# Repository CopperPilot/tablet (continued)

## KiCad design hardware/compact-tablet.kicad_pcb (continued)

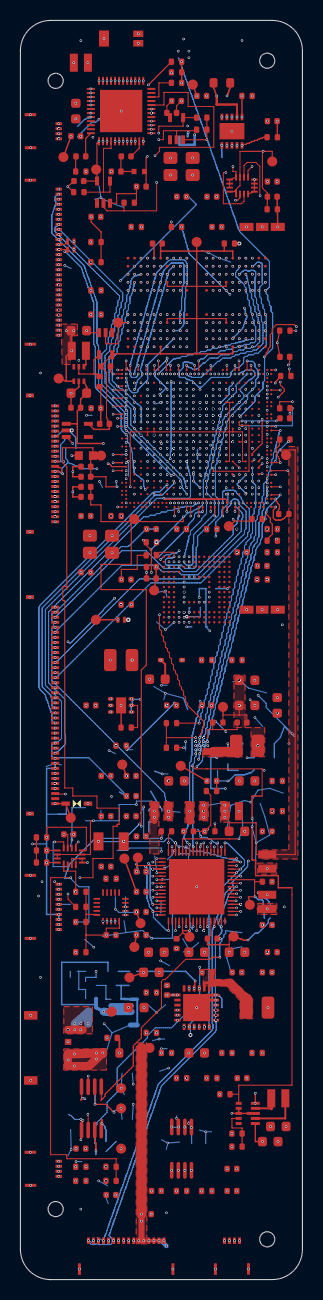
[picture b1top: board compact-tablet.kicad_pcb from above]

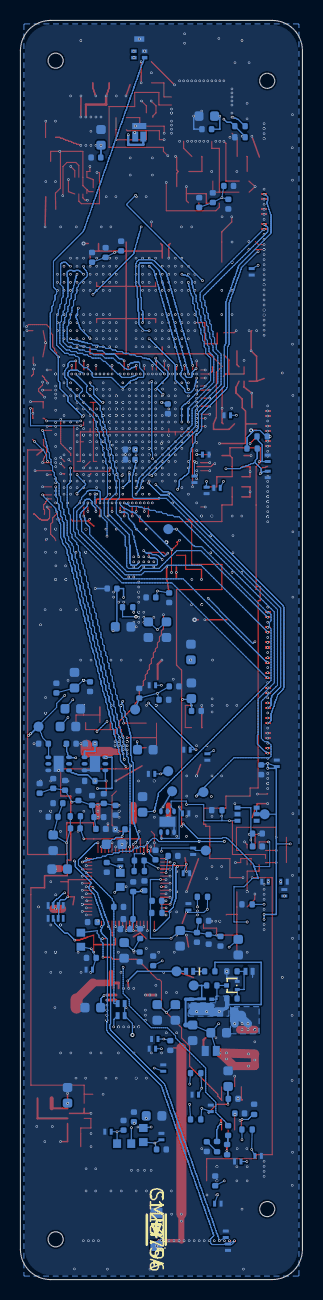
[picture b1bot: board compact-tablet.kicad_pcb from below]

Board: 8 copper layers, 28.0 x 125.0 mm, 431 parts (181 on the bottom side), 314 nets.

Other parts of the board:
H1, H2, H3, H4: MountingHole; MountingHole_1.5mm

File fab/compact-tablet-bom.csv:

Comment,Designator,Footprint,LCSC Part #
ANT3216A063R2400A,ANT1,ANT-SMD_3P-L3.1-W1.6_ANT3216A063R2400A,C412135
10uF,"C1,C2,C3,C4,C5,C6,C58,C63,C64,C70,C71,C82,C129,C130,C163,C165,C166,C167,C168,C178,C179,C180,C182",C_0603_1608Metric,C19702
1uF,"C7,C8,C9,C10,C11,C12,C29,C30,C31,C32,C33,C34,C36,C37,C38,C39,C40,C41,C43,C55,C59,C60,C62,C76,C77,C78,C79,C127,C128,C140,C142,C147,C148,C149,C151,C159,C160,C174,C177,C181,C183,C184",C_0402_1005Metric,C52923
100nF,"C13,C14,C15,C16,C17,C35,C42,C44,C45,C47,C48,C52,C56,C57,C61,C72,C75,C83,C84,C85,C86,C87,C88,C91,C92,C93,C94,C97,C98,C99,C100,C101,C105,C106,C107,C108,C109,C110,C111,C112,C113,C114,C115,C116,C117,C118,C119,C122,C123,C125,C126,C131,C132,C139,C141,C143,C144,C145,C146,C150,C152,C154,C156,C157,C158,C161,C162,C164,C169,C175,C176",C_0402_1005Metric,C1525
22uF,"C50,C51,C65,C80,C81,C89,C90,C95,C96,C102,C103,C104,C120,C121,C124",C_0603_1608Metric,C59461
1nF,"C53,C54,C73,C74,C133,C134,C135,C136,C137,C138",C_0402_1005Metric,C1523
4.7uF,"C28,C46,C153,C155",C_0603_1608Metric,C19666
10uF,"C170,C171,C172,C173",C_0402_1005Metric,C77000
2.2uF,C18,C_0402_1005Metric,C107369
1uF,C19,C_0603_1608Metric,C15849
15pF,"C20,C21,C22,C23,C24,C25",C_0402_1005Metric,C1548
10uF,C26,C_0603_1608Metric,C96446
47nF,C27,C_0402_1005Metric,C272875
4.7uF,C49,C_0402_1005Metric,C2858031
18pF,"C66,C67",C_0402_1005Metric,C1549
1.5pF,"C68,C69",C_0402_1005Metric,C1552
KW CELNM3.TK-S4S9-4L07M0-2686,D1,LED-SMD_3P-L1.9-W1.5_KW-CELMM1.TG,C17383700
"PESD5V0F1BL,315","D9,D10,D11,D12,D16,D19,D20,D21,D22,D23,D24,D25,D26,D27,D28,D32,D33,D34,D39,D40,D46,D47,D48",SOD-882_L1.0-W0.6-BI,C45961
SMF7.5A,D13,SOD-123F_L2.8-W1.8-LS3.7-RD,C123796
H36VND3B,D14,SOD-323_L1.8-W1.3-LS2.7-BI,C20615816
PTVS5V5D1BLYL,"D5,D6,D7,D8,D15,D17,D18,D29,D30,D31,D35,D36,D37,D38",SOD-882_L1.0-W0.6-BI-1,C553450
B16WS,D2,D_SOD-323,C364278
TPTVS0571P,D3,DFN-2_L1.6-W1.0-P1.10-RD,C2844712
"BAS70L,315","D43,D44,D45,D49",SOD-882_L1.0-W0.6-RD,C456141
BSMD0603L-300,F1,F0603,C5374008
FPC-0.5HF-40PWBH10,J1,FPC-SMD_40P-P0.50_FPC-0.5HF-40PWBH10,C5343289
0.5K-QX-10PWB,J2,FPC-SMD_10P-P0.50_HDGC_0.5K-QX-10PWB,C2919478
0.5K-QX-30PWB,J3,FPC-SMD_30P-P0.50_HDGC_0.5K-QX-30PWB,C2919487
FPC-0.5HF-24PWBH10,J4,FPC-SMD_24P-P0.50_XUNPU_FPC-0.5HF-24PWBH10,C5343283
DF58-4P-1.2V(21),J5,CONN-SMD_4P-P1.20_DF58-4P-1.2V-21,C20723302
0.5K-QX-16PWB,J6,FPC-SMD_16P-P0.50_HDGC_0.5K-QX-16PWB,C2919481
0.5K-QX-4PWB,"J7,J8,J9",FPC-SMD_4P-P0.50_HDGC_0.5K-QX-4PWB,C2919475
470nH,"L1,L2,L3,L4,L5",IND-SMD_L2.0-W1.6_WPN2016X,C97009
0.47uH,L10,IND-SMD_L2.0-W1.6_WPN2016X,C97009
2.2nH,L11,IND-SMD_L1.0-W0.5_LQG15HN1N6B02D,C86061
1uH,L12,IND-SMD_L2.0-W1.6_WPN2016X,C97016
120R@100MHz,"L13,L14,L15,L16,L17",L0603,C14709
470nH,L6,L_1008_2520Metric,C317620
10uH,L7,L_1008_2520Metric,C37428
1uH,L8,L_1008_2520Metric,C370610
2.2uH,L9,IND-SMD_L2.0-W1.6_WPN2016X,C97005
MSM261DCB002,MK1,MIC-SMD_5P-L2.8-W1.9_MSM261DCB002,C51928216
PPM6N20V10,Q1,DFN-6_L2.0-W2.0-P0.65-BL-EP-1,C918800
RUM002N02T2L,Q2,SOT-723_L1.2-W0.8-P0.40-LS1.2-BR,C250130
120R,R1,R_0402_1005Metric,C25079
30k,"R10,R21,R22,R35,R86,R87",R_0402_1005Metric,C25776
10k,"R4,R5,R11,R12,R27,R28,R29,R30,R31,R38,R40,R42,R43,R45,R49,R50,R51,R52,R57,R61,R64,R82,R83,R89",R_0402_1005Metric,C25744
10mR,R13,R_0603_1608Metric,C728437
75k,"R14,R36",R_0402_1005Metric,C25798
2.2k,"R2,R3,R15,R16,R17,R18,R84,R85",R_0402_1005Metric,C25879
240R,"R19,R20",R_0402_1005Metric,C25094
110k,R23,R_0402_1005Metric,C25745
0.22R,R24,R_0603_1608Metric,C858642
22R,"R25,R46,R93,R95",R_0402_1005Metric,C25092
100R,"R32,R33,R53,R54,R55,R56,R58,R59,R60",R_0402_1005Metric,C25076
47k,"R34,R91,R92",R_0402_1005Metric,C25792
200k,R37,R_0402_1005Metric,C25764
63.4k,R39,R_0402_1005Metric,C38606
49.9R,R41,R_0402_1005Metric,C25120
12k,"R44,R90",R_0402_1005Metric,C25752
300k,R47,R_0402_1005Metric,C25774
100k,"R48,R68,R69,R70,R72,R73,R74,R75,R76,R77,R78,R80,R81,R88",R_0402_1005Metric,C25741
3.3R,R6,R_0402_1005Metric,C270612
4.7k,"R62,R63,R79",R_0402_1005Metric,C25900
1k,R65,R_0402_1005Metric,C11702
1M,"R7,R66,R71",R_0402_1005Metric,C26083
0R,"R67,R94",R_0402_1005Metric,C17168
196R,R8,R_0402_1005Metric,C270631
5.1k,R9,R_0402_1005Metric,C25905
KH-PBJ-440808,"SH1,SH2",CONN-SMD_3P-L4.4-W0.8_C9900042675,C19631108
RK3566,U1,BGA-565_L15.5-W14.4-P0.40_RK3566_1,C2943786
NS4150B,"U10,U23",MSOP-8_L3.0-W3.0-P0.65-LS5.0-BL,C189961
BQ25895RTWR,U11,QFN-24_L4.0-W4.0-P0.50-TL-EP2.7,C80200
TPS63802DLAR,U12,VSON-10_L3.0-W2.0-P0.50-TL,C2845237
TLV62569ADRLR,U13,SOT-563_L1.6-W1.2-P0.50-LS1.6-BL,C398367
TPS22919DCKR,U14,SC-70-6_L2.2-W1.3-P0.65-LS2.1-BR,C2149796
TLV75533PDRVR,"U15,U21,U24",WSON-6_L2.0-W2.0-P0.65-TL-EP,C2861750
TMUX1112RSVR,U16,UQFN-16_L2.6-W1.8-P0.40-BL,C1849384
SN74LV1T34DCKR,"U17,U18,U19",SC-70-5_L2.1-W1.3-P0.65-LS2.1-BR,C78541
K4FBE3D4HM-MGCJ,U2,FBGA-200_L15.0-W10.0-BL_K4F6E3S4HM,C19188580
TLV70018DCKR,U20,SC-70-5_L2.1-W1.3-P0.65-LS2.1-BR,C133796
TMUX1511RSVR,U22,UTQFN-16_L2.6-W1.8-P0.40-BL,C2673275
LM66200DRLR,U25,SOT-583-8_L2.1-W1.2-P0.50-LS1.6-BL,C3235556
FEMDNN064G-C9A61,U3,BGA-153_L13.0-W11.5-P0.50-TL_FORESEE_FEMDME,C49284704
RK809-5,U4,QFN-68_L7.0-W7.0-P0.35-BL-EP5.5,C2939628
RTL8723DS-CG,U5,WQFN-48_L6.0-W6.0-P0.40-BL-EP4.2,C2762334
TPS61165DRVR,U6,WSON-6_L2.0-W2.0-P0.65-TL-EP,C122568
AW3641EDNR,U7,WDFN-10_L3.0-W3.0-P0.50-BL-EP,C164096
RK860-0,U8,WLCSP-20_L2.0-W1.6-R5-C4-P0.40-TL,C19188628
MPR121QR2,U9,QFN-20_L3.0-W3.0-P0.40-BL,C91322
24MHz,"Y1,Y3",Crystal_SMD_3225-4Pin_3.2x2.5mm,C70590
32.768kHz,Y2,FC-135R_L3.2-W1.5,C32346

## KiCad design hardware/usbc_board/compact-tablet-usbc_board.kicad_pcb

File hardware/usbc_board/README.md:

# USB-C Daughter Board (`usbc_board`)

2-layer 0.8 mm ENIG PCB (`25.0 x 12.0 mm`, `1.5 mm` corner radius, plated M1.4 ground mounting holes `H1` at `(2.5, 6.0)` and `H2` at `(22.5, 6.0)`) positioned at the bottom edge of the tablet (`world_position_mm: [-48.5, -162.5, 0.0]`). Provides the user-facing USB-C 5 V power sink and USB 2.0 OTG data interface (`J1`), active 6.54 V typ (`6.32 V..6.75 V`) OVP / 5.94 V typ (`5.77 V` min) recovery / 2.43 A typ (`2.19 A..2.68 A`) OCP eFuse (`U2`, `TPS259470ARPWR`, programmed by `R6=34.8k`, `R7=5.62k`, `R8=9.09k`, `R9=1.37k`, `C5=4.7nF` on `DVDT` Pin 7 setting `dV/dt = 5.11 V/ms`, local output decoupling `C4=1uF` + freewheeling Schottky clamp diode `D5=PMEG3005EL,315` on `VBUS`, and wide `>= 1.5-2.0 mm` stitched `F.Cu`/`B.Cu` polygon pours across the full `2.4 mm` length of `U2` Pads 5 and 6 feeding `J2` Pads 11..16 symmetrically, with mainboard `U11` `BQ25895RTWR` input current limit capped `<= 2.00 A` [`10.0 W` max for the `2.4 W` typ / `6.0 W` peak tablet] strictly below `U2` `I_OL(min) = 2.19 A`), 22 V standoff / 28.6 V max flat-clamp `VBUS_IN` surge TVS protection (`D3`, `ESTVS2200DRVR` `C42400188`), 50 V unswitched `VBUS_IN` decoupling (`C1`, `1 uF` 50V `GRM155R61H105KE05D` `C1518208`) + pulse-rated 0.33 W 0603 RC hot-plug snubber (`R3`, `2.2 Ohm` `ERJPA3J2R2V` + `C3`, `1 uF` 50V 0603 `CL10A105KB8NNNC` `C15849`, keeping total unswitched capacitance on `VBUS_IN` at `2.0 uF <= 2.2 uF`), compensated 6.8 kOhm 1% CC1/CC2 pull-down resistors (`R1`, `R2`, `0402WGF6801TCE` `C25917`, yielding `Rd(eff) = 6.8 kOhm || [10 kOhm R4/R5 + 10 kOhm mainboard R49/R50] = 5.075 kOhm` within `5.1 kOhm +/- 10%`), dedicated ground-referenced CC1/CC2 ESD protection (`D1`, `D2`) with `10 kOhm` series overvoltage/current-limiting isolation resistors (`R4`, `R5`), flow-through USB 2.0 D+/D- ESD protection (`U1` with Pin 5 on `USB_ESD_VBUS` decoupled by `100 nF` 50V `C2` to `GND` and biased at `~4.7 V` DC from protected `VBUS` via `1.0 kOhm` `R10` and `70 V` ultra-low-leakage blocking diode `D4` `BAS70L,315` on `USB_ESD_BIAS`), and a 16-pin 0.5 mm pitch FPC link (`J2`) to mainboard connector `J6`.

## Inter-Board 16-Pin FPC Cable Pinout (`usbc_fpc_cable`: Mainboard `J6` <-> `usbc_board` `J2`)

1-to-1 pin mapping across top-mounted `J6` (`0.5K-QX-16PWB` on `main`) and top-mounted `J2` (`0.5K-QX-16PWB` on `usbc_board`) joined by a mandated **2 oz (`0.070 mm`) heavy-copper Type-B** (opposite-side contact, Pin 1 to Pin 1) 16-pin 0.5 mm FFC cable (`FFC-0.5-16P-92MM-TYPE-B`, `0.50 A/pin` connector contact rating = `3.00 A` across 6 parallel `VBUS` contacts, protected by `U2`'s `2.43 A` typ / `2.68 A` max active OCP limit):

| `J6` Pin (Mainboard) | `J2` Pin (`usbc_board`) | Net Name | Signal / Power Function | Contact Rating & Allocation |
| :--- | :--- | :--- | :--- | :--- |
| 1 | 1 | `USB_OTG0_DP` | USB 2.0 OTG Data + (`RK3566.USB_OTG0_DP`) | 90 Ohm diff pair |
| 2 | 2 | `USB_OTG0_DM` | USB 2.0 OTG Data - (`RK3566.USB_OTG0_DM`) | 90 Ohm diff pair |
| 3 | 3 | `GND` | High-speed reference ground adjacent to D+/D- | 0.50 A contact (1 of 8 GND returns) |
| 4 | 4 | `USB_CC1` | Isolated USB-C CC1 sense (behind 10 kOhm series limiter `R4`) | Signal (`< 1 mA` fault current) |
| 5 | 5 | `USB_CC2` | Isolated USB-C CC2 sense (behind 10 kOhm series limiter `R5`) | Signal (`< 1 mA` fault current) |
| 6 | 6 | `GND` | Power return & shield ground | 0.50 A contact (2 of 8 GND returns) |
| 7 | 7 | `GND` | Power return & shield ground | 0.50 A contact (3 of 8 GND returns) |
| 8 | 8 | `GND` | Power return & shield ground | 0.50 A contact (4 of 8 GND returns) |
| 9 | 9 | `GND` | Power return & shield ground | 0.50 A contact (5 of 8 GND returns) |
| 10 | 10 | `GND` | Power return & shield ground | 0.50 A contact (6 of 6 signal GND pins = 3.00 A) |
| 11 | 11 | `VBUS` | Protected 5 V rail from `U2` (`TPS259470ARPWR` VOUT, 2.43 A typ / 2.68 A max OCP) | 0.50 A contact (1 of 6 VBUS contacts) |
| 12 | 12 | `VBUS` | Protected 5 V rail from `U2` (`TPS259470ARPWR` VOUT, 2.43 A typ / 2.68 A max OCP) | 0.50 A contact (2 of 6 VBUS contacts) |
| 13 | 13 | `VBUS` | Protected 5 V rail from `U2` (`TPS259470ARPWR` VOUT, 2.43 A typ / 2.68 A max OCP) | 0.50 A contact (3 of 6 VBUS contacts) |
| 14 | 14 | `VBUS` | Protected 5 V rail from `U2` (`TPS259470ARPWR` VOUT, 2.43 A typ / 2.68 A max OCP) | 0.50 A contact (4 of 6 VBUS contacts) |
| 15 | 15 | `VBUS` | Protected 5 V rail from `U2` (`TPS259470ARPWR` VOUT, 2.43 A typ / 2.68 A max OCP) | 0.50 A contact (5 of 6 VBUS contacts) |
| 16 | 16 | `VBUS` | Protected 5 V rail from `U2` (`TPS259470ARPWR` VOUT, 2.43 A typ / 2.68 A max OCP) | 0.50 A contact (6 of 6 VBUS contacts = 3.00 A contact rating > 2.68 A max OCP) |
| 17, 18 | 17, 18 | `GND` | Soldered mechanical reinforcement & return tabs | Shield ground (7 & 8 of 8 GND returns) |

## Complete Daughterboard BOM & Datasheet Verification

| Ref | MPN | LCSC | Value / Spec | Footprint | Function & Datasheet Margin |
| :--- | :--- | :--- | :--- | :--- | :--- |
| `J1` | `TYPE-C-31-M-12` | `C165948` | 16P USB-C Receptacle (20V/5A) | `lcsc:USB-C_SMD-TYPE-C-31-M-12_1` | Dual `VBUS_IN` (`A4B9`, `B4A9`), dual `GND` (`A1B12`, `B1A12`), 4 grounded shell tabs |
| `J2` | `0.5K-QX-16PWB` | `C2919481` | 16P 0.5mm FPC Connector | `lcsc:FPC-SMD_16P-P0.50_HDGC_0.5K-QX-16PWB` | 6x `VBUS` (`Pins 11..16`, 3.00 A contact rating > 2.68 A max U2 OCP), 8x `GND` (`Pins 3, 6..10, 17, 18`) |
| `U1` | `USBLC6-2P6` | `C2827693` | Low-C (`0.35 pF`) USB 2.0 ESD Array | `lcsc:SOT-666-6_L1.6-W1.2-P0.50-LS1.6-BL` | Flow-through on `USB_OTG0_DP/DM`; Pin 5 on `USB_ESD_VBUS` decoupled by `100 nF` `C2` to `GND` and biased at `~4.7 V` DC from `VBUS` via `R10` (`1k`) + `D4` (`BAS70L,315`) |
| `U2` | `TPS259470ARPWR` | `C3662799` | 28V, 28.3 mOhm, 5.5A Back-to-Back FET eFuse | `lcsc:VQFN-10_L2.0-W2.0-P0.45-TL` | Series OVP/OCP on `VBUS_IN` -> `VBUS`: `6.54 V` typ (`6.34 V` min) OVP cutoff, `5.94 V` typ (`5.77 V` min) recovery, `2.43 A` typ (`2.19 A..2.68 A`) active OCP, `5.11 V/ms` slew (`C5=4.7nF`) |
| `D1, D2` | `PTVS5V5D1BLYL` | `C553450` | 5.5V Bidirectional Surge TVS (`70 pF`) | `lcsc:SOD-882_L1.0-W0.6-BI-1` | Ground-referenced ESD/surge clamping on `USB_CC1_CONN` and `USB_CC2_CONN` |
| `D3` | `ESTVS2200DRVR` | `C42400188` | 22V Standoff / 28.6V Max Flat-Clamp 2000W Surge TVS | `lcsc:DFN-6_L2.0-W2.0-P0.65-BL-EP1.6` | 22 V standoff (`V_BR = 25.8 V > 20 V` USB-PD and `> 6.75 V` `U2` OVLO; flat `V_CL = 27.6 V` typ / `28.6 V` max at `70 A` 8/20 us `< 28.8 V` `U2` abs max) |
| `D4` | `BAS70L,315` | `C456141` | 70V 70mA Ultra-Low-Leakage Schottky | `lcsc:SOD-882_L1.0-W0.6-BI-1` | Blocking diode from `USB_ESD_BIAS` (`R10.2`) to `USB_ESD_VBUS` (`U1.5`/`C2.1`); biases `U1.5` at `~4.7 V` DC and blocks reverse overvoltage faults |
| `D5` | `PMEG3005EL,315` | `C282565` | 30V 0.5A (3A peak) Low-VF Schottky | `lcsc:SOD-882_L1.0-W0.6-BI-1` | Output freewheeling clamp diode (`Anode` = `GND`, `Cathode` = `VBUS`) adjacent to `U2.6` and `J2.11..16` clamping negative inductive kickback |
| `R1, R2` | `0402WGF6801TCE` | `C25917` | `6.8 kOhm` 1% 50V 62.5mW 0402 | `lcsc:R0402` | Compensated USB-C 5V/3A sink pull-downs (`6.8 kOhm || [10 kOhm R4/R5 + 10 kOhm mainboard R49/R50] = 5.075 kOhm` effective `Rd`) |
| `R3` | `ERJPA3J2R2V` | `C445778` | `2.2 Ohm` 5% **0.33W (1/3W)** Anti-Surge 0603 | `lcsc:R0603` | Pulse-rated (`>= 0.25 W`, AEC-Q200) RC hot-plug damper resistor in series with `C3` on `VBUS_DAMP` |
| `R4, R5` | `0402WGF1002TCE` | `C25744` | `10 kOhm` 1% 50V 62.5mW 0402 | `lcsc:R0402` | Series current-limiting isolation between `USB_CC1_CONN`/`USB_CC2_CONN` and `J2` Pins 4-5 (`USB_CC1`/`USB_CC2`) |
| `R6` | `0402WGF3482TCE` | `C47493` | `34.8 kOhm` 1% 50V 62.5mW 0402 | `lcsc:R0402` | Upper ladder resistor from `VBUS_IN` to `VBUS_UVLO` (`U2.1`) |
| `R7` | `0402WGF5621TCE` | `C25909` | `5.62 kOhm` 1% 50V 62.5mW 0402 | `lcsc:R0402` | Middle ladder resistor from `VBUS_UVLO` (`U2.1`) to `VBUS_OVLO` (`U2.2`, sets `V_UVLO = 4.04 V` typ rising / `3.67 V` falling) |
| `R8` | `0402WGF9091TCE` | `C11549` | `9.09 kOhm` 1% 50V 62.5mW 0402 | `lcsc:R0402` | Lower ladder resistor from `VBUS_OVLO` (`U2.2`) to `GND` (sets `V_OVLO = 6.54 V` typ [`6.32 V..6.75 V`] rising / `5.94 V` typ [`5.77 V` min] falling) |
| `R9` | `0402WGF1371TCE` | `C423239` | `1.37 kOhm` 1% 50V 62.5mW 0402 | `lcsc:R0402` | Current-limit resistor on `U2.9` (`ILM` to `GND`), setting `I_OL = 3334 / 1370 = 2.43 A` typ (`2.19 A` min, `2.68 A` max) active OCP (`> 2.00 A` charger `IINLIM` ceiling, `< 3.00 A` `J2` contact rating) |
| `R10` | `0402WGF1001TCE` | `C11702` | `1.0 kOhm` 1% 50V 62.5mW 0402 | `lcsc:R0402` | Current-limiting bias resistor from `VBUS` to `USB_ESD_BIAS` (`D4` Anode), charging `C2` (`100 nF`) in `t = 0.1 ms` |
| `C1` | `GRM155R61H105KE05D` | `C1518208` | `1 uF` **50V** X5R 0402 | `lcsc:C0402` | Unswitched HF input decoupling on `VBUS_IN` adjacent to `J1` (`50 V` rating, `> 1.75x` `D3` `28.6 V` max clamp and `2.5x` `20 V` PD fault) |
| `C2` | `CC0402KRX7R9BB104` | `C131394` | `100 nF` **50V** X7R 0402 | `lcsc:C0402` | Dedicated local ESD rail-clamp bypass on `USB_ESD_VBUS` right beside `U1.5` and `U1.2` (`50 V` rating, biased at `~4.7 V` DC) |
| `C3` | `CL10A105KB8NNNC` | `C15849` | `1 uF` **50V** X5R 0603 | `lcsc:C0603` | RC snubber capacitor in series with `R3` on `VBUS_DAMP` (`50 V` rating; `C1 + C3 = 2.0 uF <= 2.2 uF` unswitched `cSnkBulk`) |
| `C4` | `CL05A105KA5NQNC` | `C52923` | `1 uF` **25V** X5R 0402 | `lcsc:C0402` | Local output decoupling capacitor (`C_OUT`) on `VBUS` adjacent to `U2.6` and `J2.11..16` |
| `C5` | `0402B472K500NT` | `C1538` | `4.7 nF` **50V** X7R 0402 | `lcsc:C0402` | Soft-start slew-rate capacitor on `U2.7` (`VBUS_DVDT` to `GND`), setting `dV/dt = 5.11 V/ms` (`t_dVdT = 0.98 ms`) |
| `H1, H2` | `MountingHole_Pad` | — | M1.4 Plated Ground Mounting Holes (`1.5 mm` drill) | `lcsc:MountingHole_1.5mm` | Chassis/return ground tie at `(2.5, 6.0)` and `(22.5, 6.0)` |

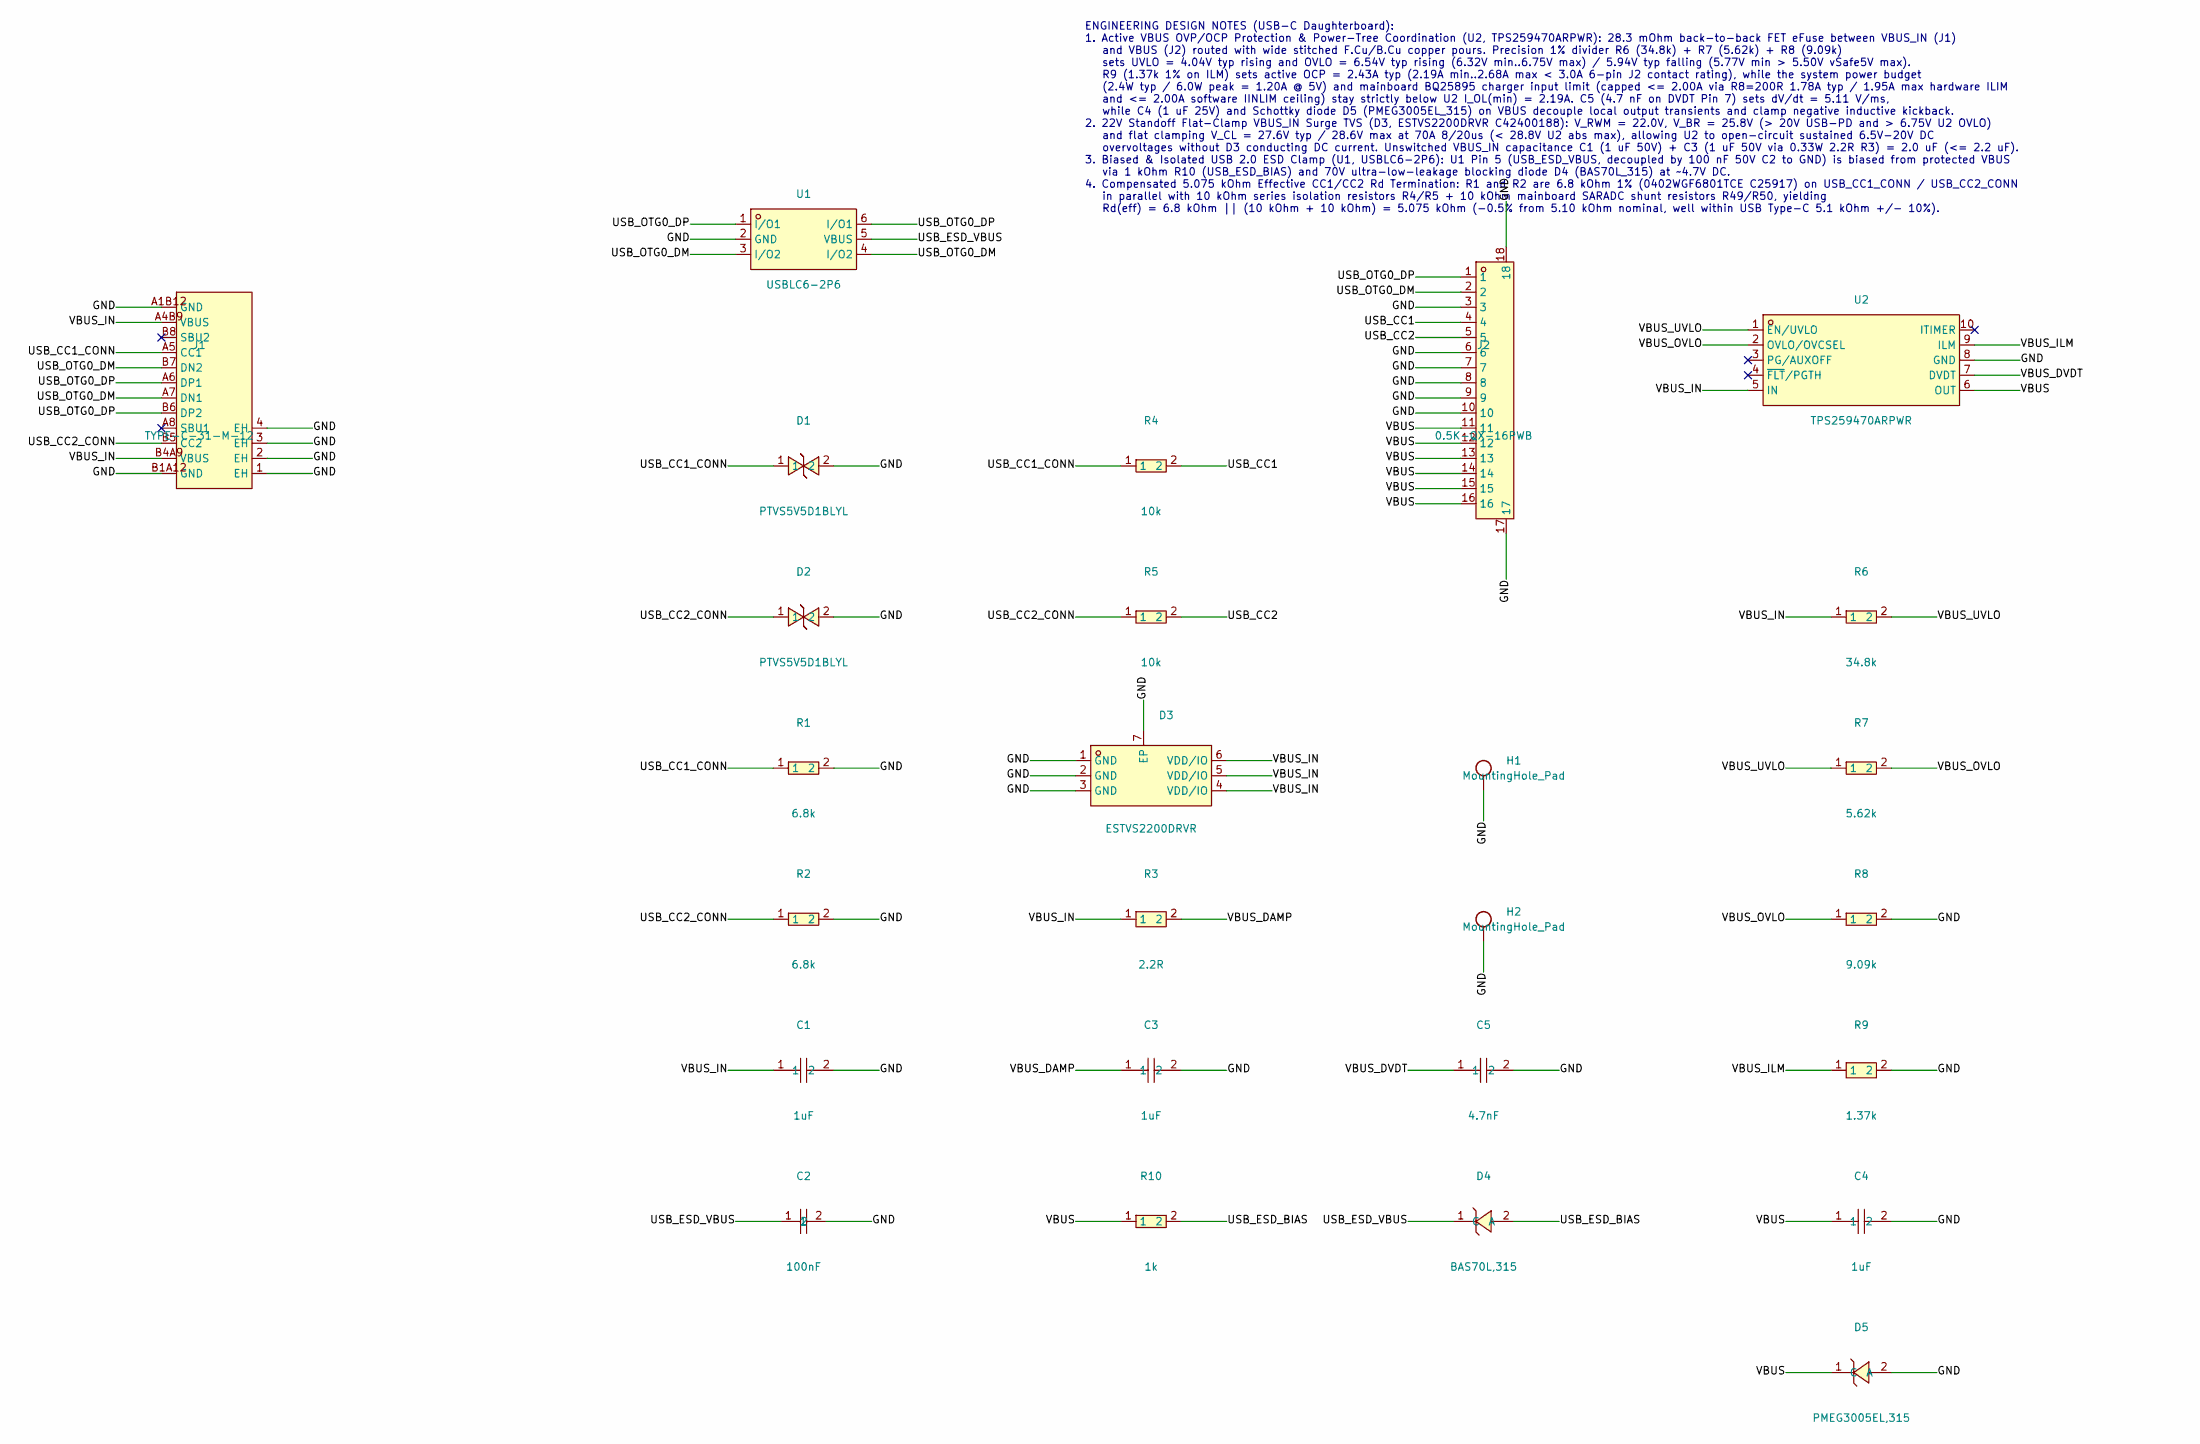
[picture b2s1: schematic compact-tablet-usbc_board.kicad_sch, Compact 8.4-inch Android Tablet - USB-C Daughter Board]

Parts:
C1: 1uF; C0402; MPN GRM155R61H105KE05D; LCSC C1518208
C2: 100nF; C0402; MPN CC0402KRX7R9BB104; LCSC C131394
C3: 1uF; C0603; MPN CL10A105KB8NNNC; LCSC C15849
C4: 1uF; C0402; MPN CL05A105KA5NQNC; LCSC C52923
C5: 4.7nF; C0402; MPN 0402B472K500NT; LCSC C1538
D1, D2: PTVS5V5D1BLYL; SOD-882_L1.0-W0.6-BI-1; MPN PTVS5V5D1BLYL; LCSC C553450
D3: ESTVS2200DRVR; DFN-6_L2.0-W2.0-P0.65-BL-EP1.6; MPN ESTVS2200DRVR; LCSC C42400188
D4: BAS70L,315; SOD-882_L1.0-W0.6-BI-1; MPN BAS70L,315; LCSC C456141
D5: PMEG3005EL,315; SOD-882_L1.0-W0.6-BI-1; MPN PMEG3005EL,315; LCSC C282565
H1, H2: MountingHole_Pad; MountingHole_1.5mm
J1: TYPE-C-31-M-12; USB-C_SMD-TYPE-C-31-M-12_1; MPN TYPE-C-31-M-12; LCSC C165948
J2: 0.5K-QX-16PWB; FPC-SMD_16P-P0.50_HDGC_0.5K-QX-16PWB; MPN 0.5K-QX-16PWB; LCSC C2919481
R1, R2: 6.8k; R0402; MPN 0402WGF6801TCE; LCSC C25917
R3: 2.2R; R0603; MPN ERJPA3J2R2V; LCSC C445778
R4, R5: 10k; R0402; MPN 0402WGF1002TCE; LCSC C25744
R6: 34.8k; R0402; MPN 0402WGF3482TCE; LCSC C47493
R7: 5.62k; R0402; MPN 0402WGF5621TCE; LCSC C25909
R8: 9.09k; R0402; MPN 0402WGF9091TCE; LCSC C11549
R9: 1.37k; R0402; MPN 0402WGF1371TCE; LCSC C423239
R10: 1k; R0402; MPN 0402WGF1001TCE; LCSC C11702
U1: USBLC6-2P6; SOT-666-6_L1.6-W1.2-P0.50-LS1.6-BL; MPN USBLC6-2P6; LCSC C2827693
U2: TPS259470ARPWR; VQFN-10_L2.0-W2.0-P0.45-TL; MPN TPS259470ARPWR; LCSC C3662799

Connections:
/GND: C1.2, C2.2, C3.2, C4.2, C5.2, D1.2, D2.2, D3.1 (GND), D3.2 (GND), D3.3 (GND), D3.7 (EP), D5.2 (A), H1.1, H2.1, J1.1 (EH), J1.2 (EH), J1.3 (EH), J1.4 (EH), J1.A1B12 (GND), J1.B1A12 (GND), J2.3, J2.6, J2.7, J2.8, J2.9, J2.10, J2.17, J2.18, R1.2, R2.2, R8.2, R9.2, U1.2 (GND), U2.8 (GND)
/USB_CC1: J2.4, R4.2
/USB_CC1_CONN: D1.1, J1.A5 (CC1), R1.1, R4.1
/USB_CC2: J2.5, R5.2
/USB_CC2_CONN: D2.1, J1.B5 (CC2), R2.1, R5.1
/USB_ESD_BIAS: D4.2 (A), R10.2
/USB_ESD_VBUS: C2.1, D4.1 (C), U1.5 (VBUS)
/USB_OTG0_DM: J1.A7 (DN1), J1.B7 (DN2), J2.2, U1.3 (I/O2), U1.4 (I/O2)
/USB_OTG0_DP: J1.A6 (DP1), J1.B6 (DP2), J2.1, U1.1 (I/O1), U1.6 (I/O1)
/VBUS: C4.1, D5.1 (C), J2.11, J2.12, J2.13, J2.14, J2.15, J2.16, R10.1, U2.6 (OUT)
/VBUS_DAMP: C3.1, R3.2
/VBUS_DVDT: C5.1, U2.7 (DVDT)
/VBUS_ILM: R9.1, U2.9 (ILM)
/VBUS_IN: C1.1, D3.4 (VDD/IO), D3.5 (VDD/IO), D3.6 (VDD/IO), J1.A4B9 (VBUS), J1.B4A9 (VBUS), R3.1, R6.1, U2.5 (IN)
/VBUS_OVLO: R7.2, R8.1, U2.2 (OVLO/OVCSEL)
/VBUS_UVLO: R6.2, R7.1, U2.1 (EN/UVLO)

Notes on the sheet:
ENGINEERING DESIGN NOTES (USB-C Daughterboard): 1. Active VBUS OVP/OCP Protection & Power-Tree Coordination (U2, TPS259470ARPWR): 28.3 mOhm back-to-back FET eFuse between VBUS_IN (J1) and VBUS (J2) routed with wide stitched F.Cu/B.Cu copper pours. Precision 1% divider R6 (34.8k) + R7 (5.62k) + R8 (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

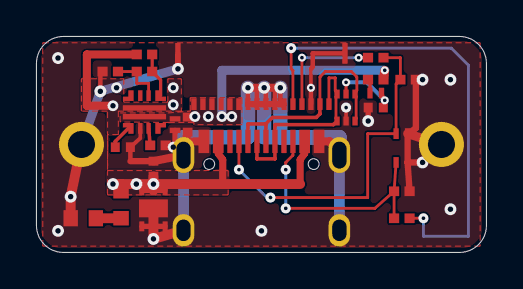
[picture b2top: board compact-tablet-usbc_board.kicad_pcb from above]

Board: 2 copper layers, 25.0 x 12.0 mm, 26 parts (0 on the bottom side), 16 nets.
